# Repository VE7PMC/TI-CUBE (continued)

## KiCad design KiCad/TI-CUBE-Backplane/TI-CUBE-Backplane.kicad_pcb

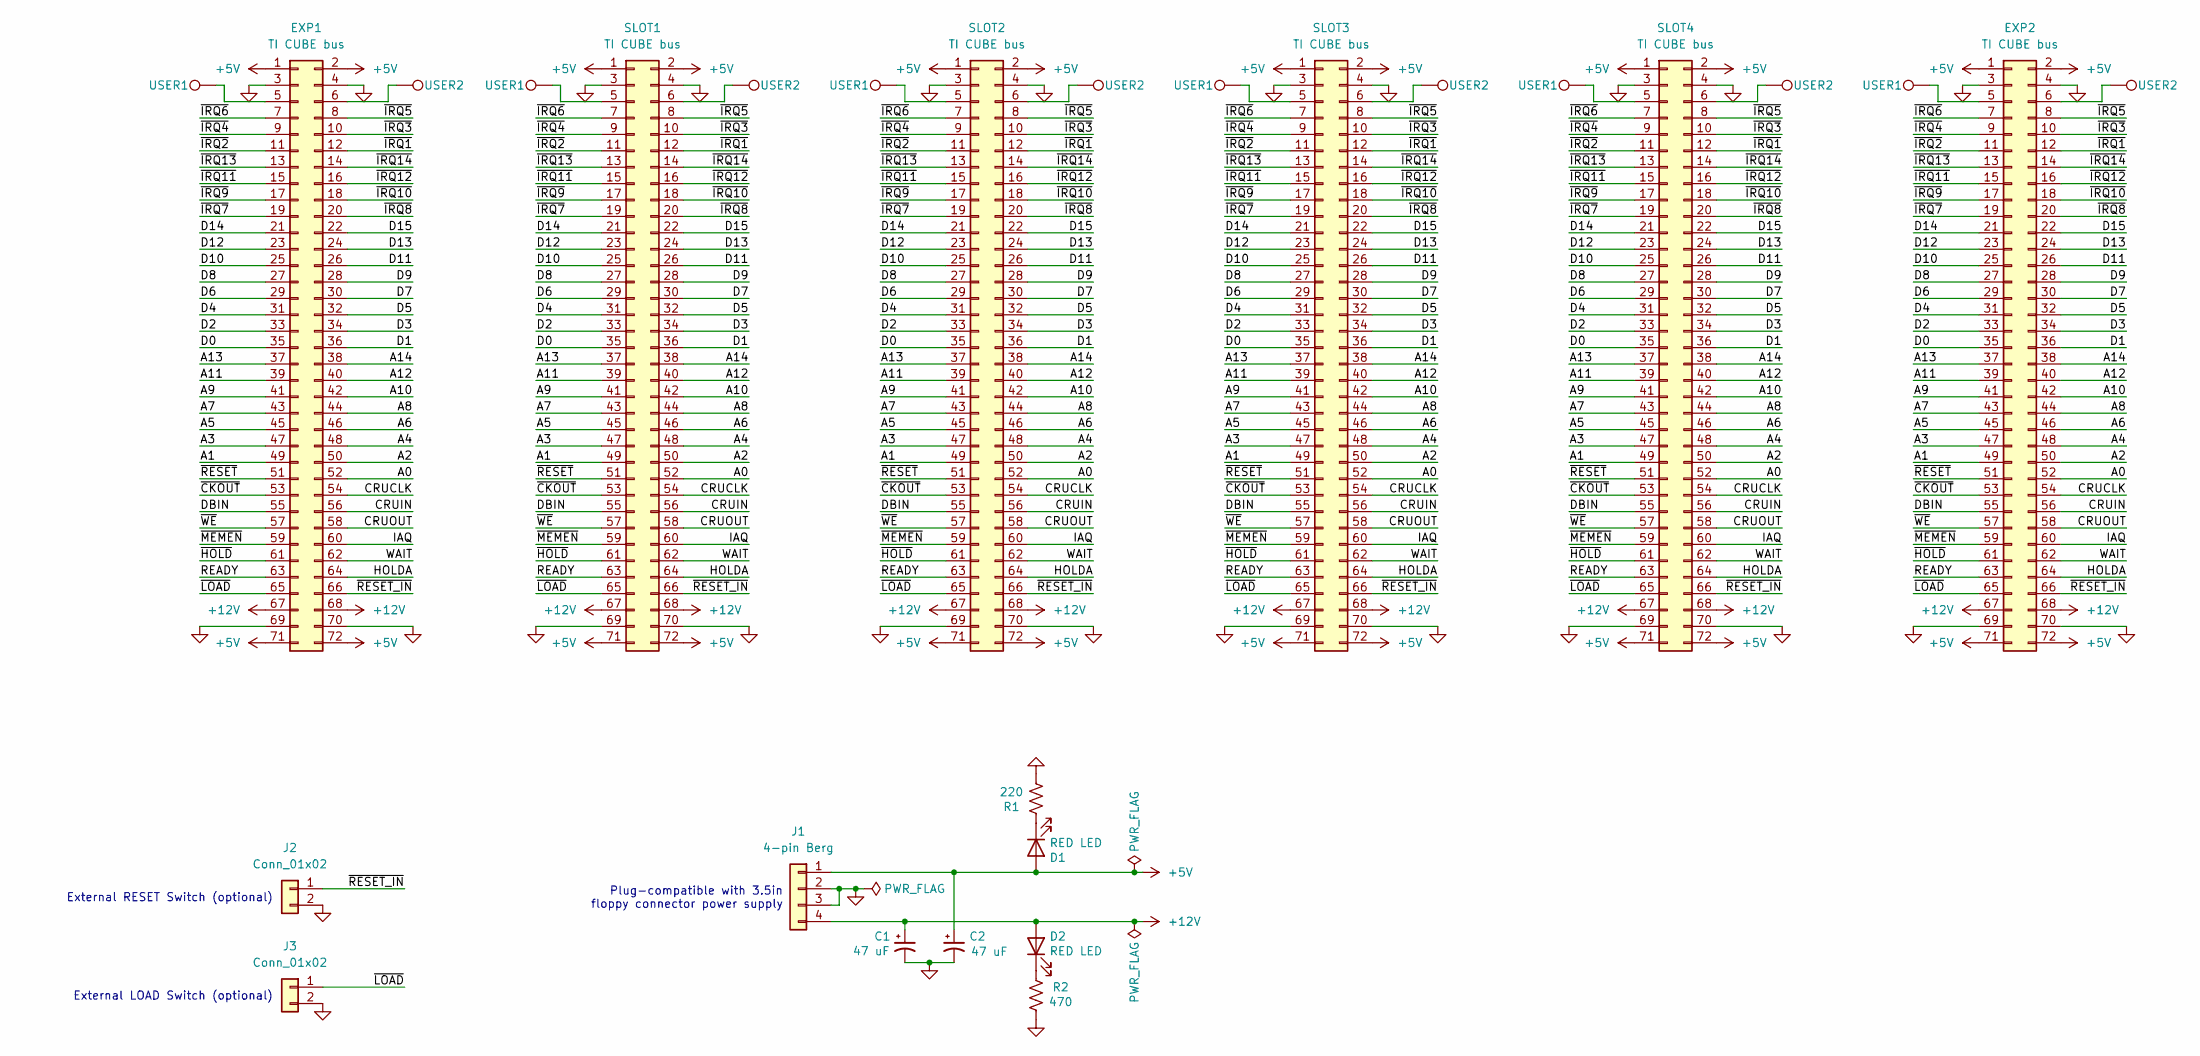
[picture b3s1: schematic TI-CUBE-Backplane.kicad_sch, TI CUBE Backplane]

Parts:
C1, C2: 47 uF; CP_Radial_D6.3mm_P2.50mm
D1, D2: RED LED; LED_D3.0mm
EXP1: TI CUBE bus; PinHeader_2x36_P2.54mm_Horizontal
EXP2: TI CUBE bus; PinSocket_2x36_P2.54mm_Horizontal
J1: 4-pin Berg; TE_171825-4
J2, J3: Conn_01x02; PinHeader_1x02_P2.54mm_Vertical
R1: 220; R_Axial_DIN0207_L6.3mm_D2.5mm_P10.16mm_Horizontal
R2: 470; R_Axial_DIN0207_L6.3mm_D2.5mm_P10.16mm_Horizontal
SLOT1, SLOT2, SLOT3, SLOT4: TI CUBE bus; PinSocket_2x36_P2.54mm_Vertical
USER1, USER4, USER5, USER7, USER9, USER11: USER1; TestPoint_THTPad_D1.5mm_Drill0.7mm
USER2, USER3, USER6, USER8, USER10, USER12: USER2; TestPoint_THTPad_D1.5mm_Drill0.7mm

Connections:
+5V: C2.1, D1.2 (A), EXP1.1, EXP1.2, EXP1.71, EXP1.72, EXP2.1, EXP2.2, EXP2.71, EXP2.72, J1.1, SLOT1.1, SLOT1.2, SLOT1.71, SLOT1.72, SLOT2.1, SLOT2.2, SLOT2.71, SLOT2.72, SLOT3.1, SLOT3.2, SLOT3.71, SLOT3.72, SLOT4.1, SLOT4.2, SLOT4.71, SLOT4.72
+12V: C1.1, D2.2 (A), EXP1.67, EXP1.68, EXP2.67, EXP2.68, J1.4, SLOT1.67, SLOT1.68, SLOT2.67, SLOT2.68, SLOT3.67, SLOT3.68, SLOT4.67, SLOT4.68
/A0: EXP1.52, EXP2.52, SLOT1.52, SLOT2.52, SLOT3.52, SLOT4.52
/A1: EXP1.49, EXP2.49, SLOT1.49, SLOT2.49, SLOT3.49, SLOT4.49
/A2: EXP1.50, EXP2.50, SLOT1.50, SLOT2.50, SLOT3.50, SLOT4.50
/A3: EXP1.47, EXP2.47, SLOT1.47, SLOT2.47, SLOT3.47, SLOT4.47
/A4: EXP1.48, EXP2.48, SLOT1.48, SLOT2.48, SLOT3.48, SLOT4.48
/A5: EXP1.45, EXP2.45, SLOT1.45, SLOT2.45, SLOT3.45, SLOT4.45
/A6: EXP1.46, EXP2.46, SLOT1.46, SLOT2.46, SLOT3.46, SLOT4.46
/A7: EXP1.43, EXP2.43, SLOT1.43, SLOT2.43, SLOT3.43, SLOT4.43
/A8: EXP1.44, EXP2.44, SLOT1.44, SLOT2.44, SLOT3.44, SLOT4.44
/A9: EXP1.41, EXP2.41, SLOT1.41, SLOT2.41, SLOT3.41, SLOT4.41
/A10: EXP1.42, EXP2.42, SLOT1.42, SLOT2.42, SLOT3.42, SLOT4.42
/A11: EXP1.39, EXP2.39, SLOT1.39, SLOT2.39, SLOT3.39, SLOT4.39
/A12: EXP1.40, EXP2.40, SLOT1.40, SLOT2.40, SLOT3.40, SLOT4.40
/A13: EXP1.37, EXP2.37, SLOT1.37, SLOT2.37, SLOT3.37, SLOT4.37
/A14: EXP1.38, EXP2.38, SLOT1.38, SLOT2.38, SLOT3.38, SLOT4.38
/CRUCLK: EXP1.54, EXP2.54, SLOT1.54, SLOT2.54, SLOT3.54, SLOT4.54
/CRUIN: EXP1.56, EXP2.56, SLOT1.56, SLOT2.56, SLOT3.56, SLOT4.56
/CRUOUT: EXP1.58, EXP2.58, SLOT1.58, SLOT2.58, SLOT3.58, SLOT4.58
/D0: EXP1.35, EXP2.35, SLOT1.35, SLOT2.35, SLOT3.35, SLOT4.35
/D1: EXP1.36, EXP2.36, SLOT1.36, SLOT2.36, SLOT3.36, SLOT4.36
/D2: EXP1.33, EXP2.33, SLOT1.33, SLOT2.33, SLOT3.33, SLOT4.33
/D3: EXP1.34, EXP2.34, SLOT1.34, SLOT2.34, SLOT3.34, SLOT4.34
/D4: EXP1.31, EXP2.31, SLOT1.31, SLOT2.31, SLOT3.31, SLOT4.31
/D5: EXP1.32, EXP2.32, SLOT1.32, SLOT2.32, SLOT3.32, SLOT4.32
/D6: EXP1.29, EXP2.29, SLOT1.29, SLOT2.29, SLOT3.29, SLOT4.29
/D7: EXP1.30, EXP2.30, SLOT1.30, SLOT2.30, SLOT3.30, SLOT4.30
/D8: EXP1.27, EXP2.27, SLOT1.27, SLOT2.27, SLOT3.27, SLOT4.27
/D9: EXP1.28, EXP2.28, SLOT1.28, SLOT2.28, SLOT3.28, SLOT4.28
/D10: EXP1.25, EXP2.25, SLOT1.25, SLOT2.25, SLOT3.25, SLOT4.25
/D11: EXP1.26, EXP2.26, SLOT1.26, SLOT2.26, SLOT3.26, SLOT4.26
/D12: EXP1.23, EXP2.23, SLOT1.23, SLOT2.23, SLOT3.23, SLOT4.23
/D13: EXP1.24, EXP2.24, SLOT1.24, SLOT2.24, SLOT3.24, SLOT4.24
/D14: EXP1.21, EXP2.21, SLOT1.21, SLOT2.21, SLOT3.21, SLOT4.21
/D15: EXP1.22, EXP2.22, SLOT1.22, SLOT2.22, SLOT3.22, SLOT4.22
/DBIN: EXP1.55, EXP2.55, SLOT1.55, SLOT2.55, SLOT3.55, SLOT4.55
/HOLDA: EXP1.64, EXP2.64, SLOT1.64, SLOT2.64, SLOT3.64, SLOT4.64
/IAQ: EXP1.60, EXP2.60, SLOT1.60, SLOT2.60, SLOT3.60, SLOT4.60
/READY: EXP1.63, EXP2.63, SLOT1.63, SLOT2.63, SLOT3.63, SLOT4.63
/WAIT: EXP1.62, EXP2.62, SLOT1.62, SLOT2.62, SLOT3.62, SLOT4.62
/~CKOUT: EXP1.53, EXP2.53, SLOT1.53, SLOT2.53, SLOT3.53, SLOT4.53
/~HOLD: EXP1.61, EXP2.61, SLOT1.61, SLOT2.61, SLOT3.61, SLOT4.61
/~IRQ1: EXP1.12, EXP2.12, SLOT1.12, SLOT2.12, SLOT3.12, SLOT4.12
/~IRQ2: EXP1.11, EXP2.11, SLOT1.11, SLOT2.11, SLOT3.11, SLOT4.11
/~IRQ3: EXP1.10, EXP2.10, SLOT1.10, SLOT2.10, SLOT3.10, SLOT4.10
/~IRQ4: EXP1.9, EXP2.9, SLOT1.9, SLOT2.9, SLOT3.9, SLOT4.9
/~IRQ5: EXP1.8, EXP2.8, SLOT1.8, SLOT2.8, SLOT3.8, SLOT4.8
/~IRQ6: EXP1.7, EXP2.7, SLOT1.7, SLOT2.7, SLOT3.7, SLOT4.7
/~IRQ7: EXP1.19, EXP2.19, SLOT1.19, SLOT2.19, SLOT3.19, SLOT4.19
/~IRQ8: EXP1.20, EXP2.20, SLOT1.20, SLOT2.20, SLOT3.20, SLOT4.20
/~IRQ9: EXP1.17, EXP2.17, SLOT1.17, SLOT2.17, SLOT3.17, SLOT4.17
/~IRQ10: EXP1.18, EXP2.18, SLOT1.18, SLOT2.18, SLOT3.18, SLOT4.18
/~IRQ11: EXP1.15, EXP2.15, SLOT1.15, SLOT2.15, SLOT3.15, SLOT4.15
/~IRQ12: EXP1.16, EXP2.16, SLOT1.16, SLOT2.16, SLOT3.16, SLOT4.16
/~IRQ13: EXP1.13, EXP2.13, SLOT1.13, SLOT2.13, SLOT3.13, SLOT4.13
/~IRQ14: EXP1.14, EXP2.14, SLOT1.14, SLOT2.14, SLOT3.14, SLOT4.14
/~LOAD: EXP1.65, EXP2.65, J3.1, SLOT1.65, SLOT2.65, SLOT3.65, SLOT4.65
/~MEMEN: EXP1.59, EXP2.59, SLOT1.59, SLOT2.59, SLOT3.59, SLOT4.59
/~RESET_IN: EXP1.66, EXP2.66, J2.1, SLOT1.66, SLOT2.66, SLOT3.66, SLOT4.66
/~RESET: EXP1.51, EXP2.51, SLOT1.51, SLOT2.51, SLOT3.51, SLOT4.51
/~WE: EXP1.57, EXP2.57, SLOT1.57, SLOT2.57, SLOT3.57, SLOT4.57
GND: C1.2, C2.2, EXP1.3, EXP1.4, EXP1.69, EXP1.70, EXP2.3, EXP2.4, EXP2.69, EXP2.70, J1.2, J1.3, J2.2, J3.2, R1.1, R2.1, SLOT1.3, SLOT1.4, SLOT1.69, SLOT1.70, SLOT2.3, SLOT2.4, SLOT2.69, SLOT2.70, SLOT3.3, SLOT3.4, SLOT3.69, SLOT3.70, SLOT4.3, SLOT4.4, SLOT4.69, SLOT4.70
unnamed: D1.1 (K), R1.2
unnamed: D2.1 (K), R2.2
unnamed: EXP1.5, USER1.1
unnamed: EXP1.6, USER2.1
unnamed: EXP2.5, USER11.1
unnamed: EXP2.6, USER12.1
unnamed: SLOT1.5, USER4.1
unnamed: SLOT1.6, USER3.1
unnamed: SLOT2.5, USER5.1
unnamed: SLOT2.6, USER6.1
unnamed: SLOT3.5, USER7.1
unnamed: SLOT3.6, USER8.1
unnamed: SLOT4.5, USER9.1
unnamed: SLOT4.6, USER10.1

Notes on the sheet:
Plug-compatible with 3.5in floppy connector power supply
External LOAD Switch (optional)
External RESET Switch (optional)

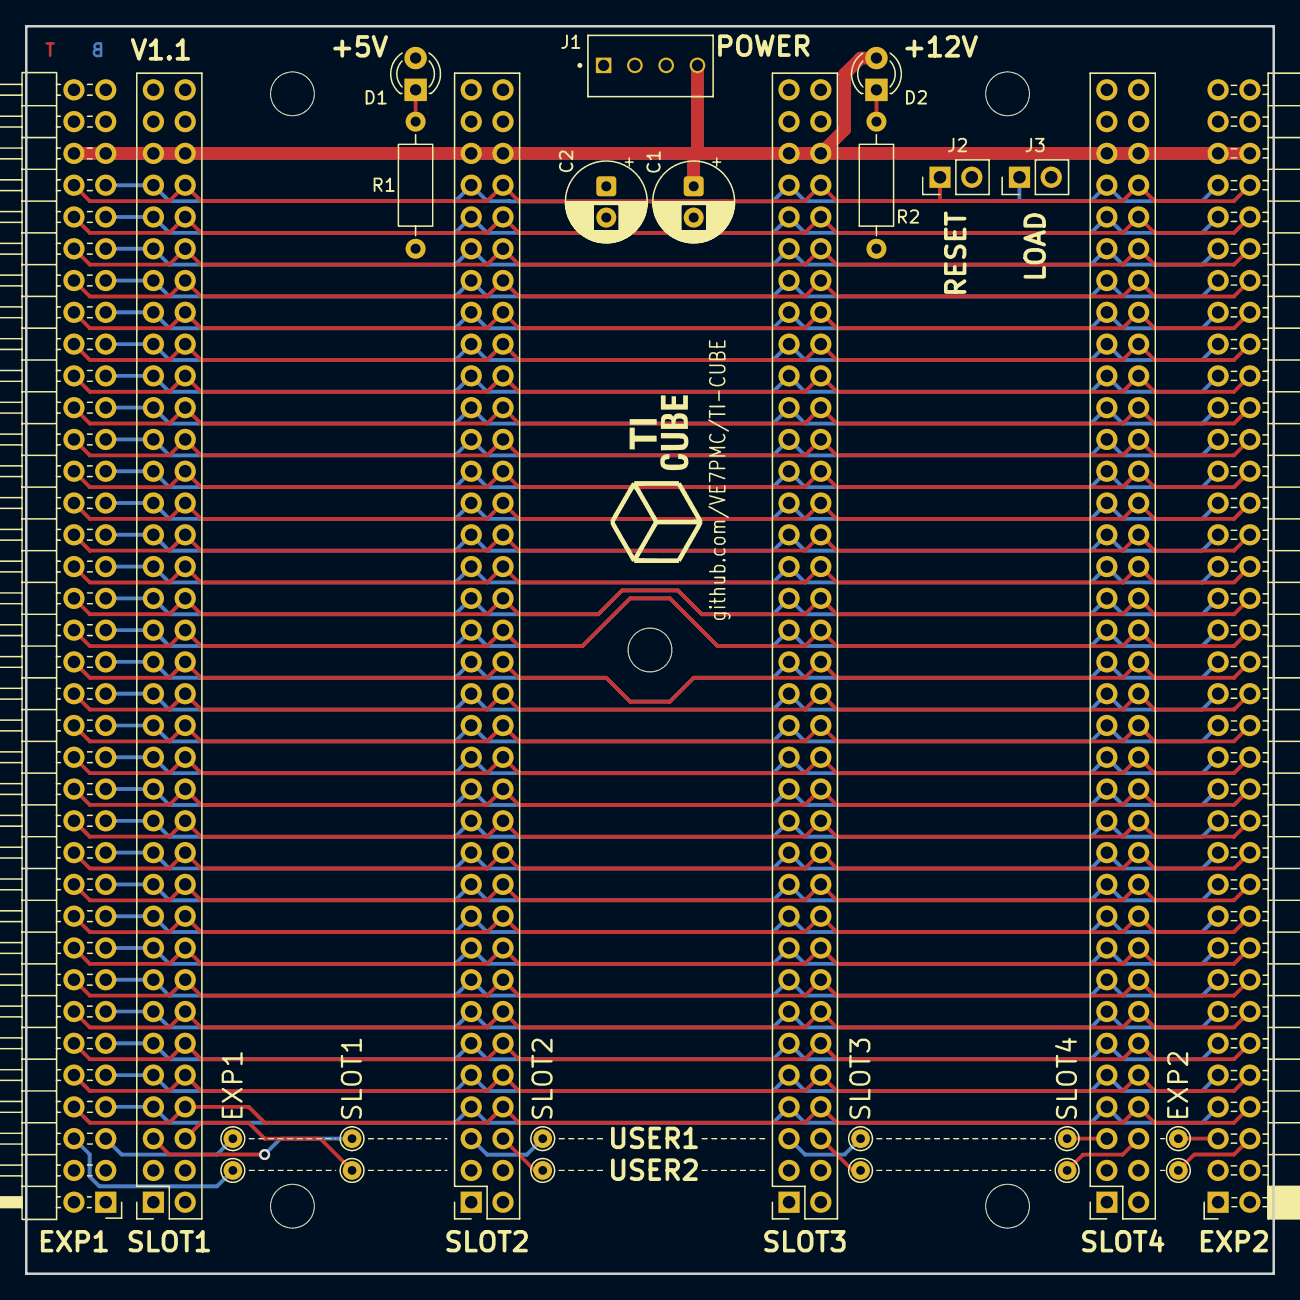
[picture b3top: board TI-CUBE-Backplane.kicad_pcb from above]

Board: 4 copper layers, 99.7 x 99.7 mm, 27 parts (0 on the bottom side), 77 nets.

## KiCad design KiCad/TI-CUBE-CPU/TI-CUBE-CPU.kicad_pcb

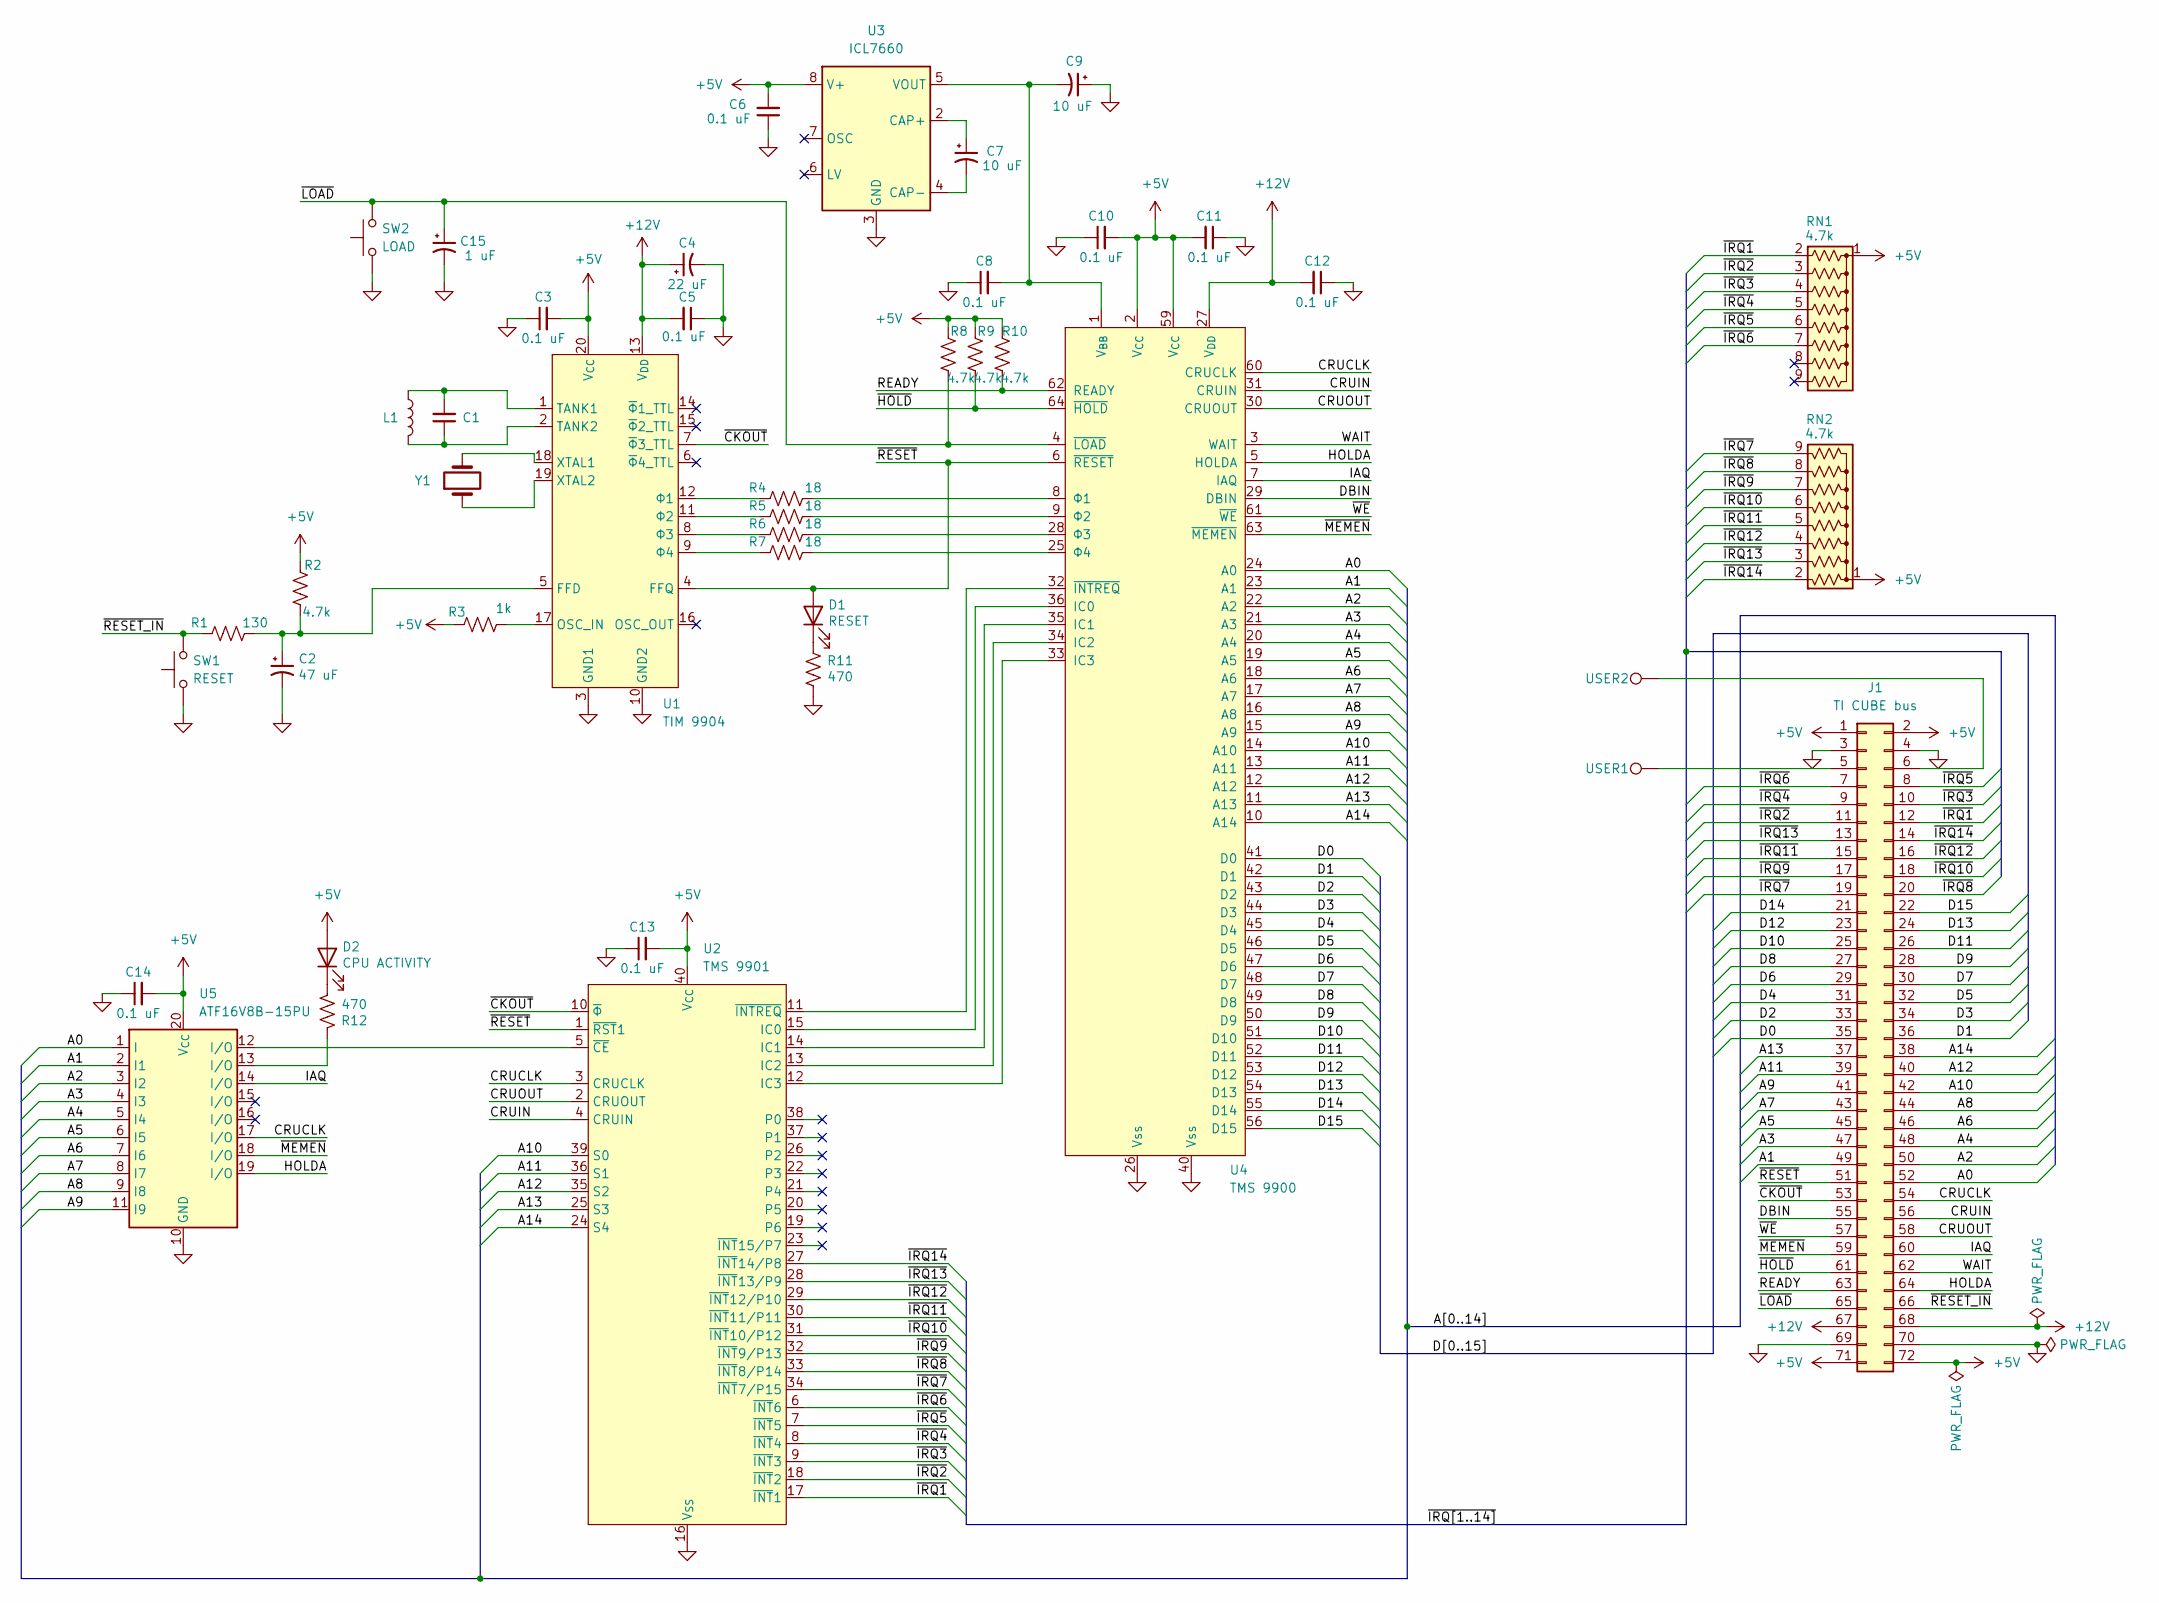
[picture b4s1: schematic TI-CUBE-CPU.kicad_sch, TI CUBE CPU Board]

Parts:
C1: 18 pF; C_Ceramic_Cap_P2.50mm
C2: 47 uF; CP_Radial_D5.0mm_P2.50mm
C3, C5, C6, C8, C10, C11, C12, C13, C14: 0.1 uF; C_Ceramic_Cap_P2.50mm
C4: 22 uF; CP_Radial_D5.0mm_P2.50mm
C7, C9: 10 uF; CP_Radial_D5.0mm_P2.50mm
C15: 1 uF; CP_Radial_D5.0mm_P2.50mm
D1: RESET; LED_D3.0mm_Horizontal_O1.27mm_Z2.0mm
D2: CPU ACTIVITY; LED_D3.0mm_Horizontal_O1.27mm_Z2.0mm
J1: TI CUBE bus; PinHeader_2x36_P2.54mm_Horizontal
L1: 0.47 uH; L_Axial_L6.6mm_D2.7mm_P2.54mm_Vertical_Vishay_IM-2
R1: 130; R_Axial_DIN0207_L6.3mm_D2.5mm_P7.62mm_Horizontal
R2, R8, R9, R10: 4.7k; R_Axial_DIN0207_L6.3mm_D2.5mm_P7.62mm_Horizontal
R3: 1k; R_Axial_DIN0207_L6.3mm_D2.5mm_P7.62mm_Horizontal
R4, R5, R6, R7: 18; R_Axial_DIN0207_L6.3mm_D2.5mm_P7.62mm_Horizontal
R11, R12: 470; R_Axial_DIN0207_L6.3mm_D2.5mm_P7.62mm_Horizontal
RN1, RN2: 4.7k; R_Array_SIP9
SW1: RESET; SW_SPST_Omron_B3F-315x_Angled
SW2: LOAD; SW_SPST_Omron_B3F-315x_Angled
U1: TIM 9904; DIP-20_W7.62mm
U2: TMS 9901; DIP-40_W15.24mm
U3: ICL7660; DIP-8_W7.62mm
U4: TMS 9900; DIP-64_W22.86mm
U5: ATF16V8B-15PU; DIP-20_W7.62mm
USER1: USER1; TestPoint_THTPad_D1.5mm_Drill0.7mm
USER2: USER2; TestPoint_THTPad_D1.5mm_Drill0.7mm
Y1: 48 MHz; Crystal_HC49-4H_Vertical

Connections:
+5V: C3.2, C6.2, C10.2, C11.2, C13.2, C14.2, D2.2 (A), J1.1, J1.2, J1.71, J1.72, R2.2, R3.2, R8.2, R9.2, R10.2, RN1.1 (common), RN2.1 (common), U1.20 (V_{CC}), U2.40 (V_{CC}), U3.8 (V+), U4.2 (V_{CC}), U4.59 (V_{CC}), U5.20 (V_{CC})
+12V: C4.1, C5.2, C12.2, J1.67, J1.68, U1.13 (V_{DD}), U4.27 (V_{DD})
/A0: J1.52, U4.24 (A0), U5.1 (I)
/A1: J1.49, U4.23 (A1), U5.2 (I1)
/A2: J1.50, U4.22 (A2), U5.3 (I2)
/A3: J1.47, U4.21 (A3), U5.4 (I3)
/A4: J1.48, U4.20 (A4), U5.5 (I4)
/A5: J1.45, U4.19 (A5), U5.6 (I5)
/A6: J1.46, U4.18 (A6), U5.7 (I6)
/A7: J1.43, U4.17 (A7), U5.8 (I7)
/A8: J1.44, U4.16 (A8), U5.9 (I8)
/A9: J1.41, U4.15 (A9), U5.11 (I9)
/A10: J1.42, U2.39 (S0), U4.14 (A10)
/A11: J1.39, U2.36 (S1), U4.13 (A11)
/A12: J1.40, U2.35 (S2), U4.12 (A12)
/A13: J1.37, U2.25 (S3), U4.11 (A13)
/A14: J1.38, U2.24 (S4), U4.10 (A14)
/CRUCLK: J1.54, U2.3 (CRUCLK), U4.60 (CRUCLK), U5.17 (I/O)
/CRUIN: J1.56, U2.4 (CRUIN), U4.31 (CRUIN)
/CRUOUT: J1.58, U2.2 (CRUOUT), U4.30 (CRUOUT)
/D0: J1.35, U4.41 (D0)
/D1: J1.36, U4.42 (D1)
/D2: J1.33, U4.43 (D2)
/D3: J1.34, U4.44 (D3)
/D4: J1.31, U4.45 (D4)
/D5: J1.32, U4.46 (D5)
/D6: J1.29, U4.47 (D6)
/D7: J1.30, U4.48 (D7)
/D8: J1.27, U4.49 (D8)
/D9: J1.28, U4.50 (D9)
/D10: J1.25, U4.51 (D10)
/D11: J1.26, U4.52 (D11)
/D12: J1.23, U4.53 (D12)
/D13: J1.24, U4.54 (D13)
/D14: J1.21, U4.55 (D14)
/D15: J1.22, U4.56 (D15)
/DBIN: J1.55, U4.29 (DBIN)
/HOLDA: J1.64, U4.5 (HOLDA), U5.19 (I/O)
/IAQ: J1.60, U4.7 (IAQ), U5.14 (I/O)
/READY: J1.63, R10.1, U4.62 (READY)
/WAIT: J1.62, U4.3 (WAIT)
/~CKOUT: J1.53, U1.7 (~Φ3_TTL), U2.10 (~Φ)
/~HOLD: J1.61, R9.1, U4.64 (~HOLD)
/~IRQ1: J1.12, RN1.2 (R1), U2.17 (~INT1)
/~IRQ2: J1.11, RN1.3 (R2), U2.18 (~INT2)
/~IRQ3: J1.10, RN1.4 (R3), U2.9 (~INT3)
/~IRQ4: J1.9, RN1.5 (R4), U2.8 (~INT4)
/~IRQ5: J1.8, RN1.6 (R5), U2.7 (~INT5)
/~IRQ6: J1.7, RN1.7 (R6), U2.6 (~INT6)
/~IRQ7: J1.19, RN2.9 (R8), U2.34 (~INT7/P15)
/~IRQ8: J1.20, RN2.8 (R7), U2.33 (~INT8/P14)
/~IRQ9: J1.17, RN2.7 (R6), U2.32 (~INT9/P13)
/~IRQ10: J1.18, RN2.6 (R5), U2.31 (~INT10/P12)
/~IRQ11: J1.15, RN2.5 (R4), U2.30 (~INT11/P11)
/~IRQ12: J1.16, RN2.4 (R3), U2.29 (~INT12/P10)
/~IRQ13: J1.13, RN2.3 (R2), U2.28 (~INT13/P9)
/~IRQ14: J1.14, RN2.2 (R1), U2.27 (~INT14/P8)
/~LOAD: C15.1, J1.65, R8.1, SW2.2, U4.4 (~LOAD)
/~MEMEN: J1.59, U4.63 (~MEMEN), U5.18 (I/O)
/~RESET_IN: J1.66, R1.1, SW1.2
/~RESET: D1.2 (A), J1.51, U1.4 (FFQ), U2.1 (~RST1), U4.6 (~RESET)
/~WE: J1.57, U4.61 (~WE)
GND: C2.2, C3.1, C4.2, C5.1, C6.1, C8.1, C9.1, C10.1, C11.1, C12.1, C13.1, C14.1, C15.2, J1.3, J1.4, J1.69, J1.70, R11.1, SW1.1, SW2.1, U1.3 (GND1), U1.10 (GND2), U2.16 (V_{SS}), U3.3 (GND), U4.26 (Vss), U4.40 (Vss), U5.10 (GND)
unnamed: D1.1 (K), R11.2
unnamed: D2.1 (K), R12.1
unnamed: J1.5, USER1.1
unnamed: J1.6, USER2.1
unnamed: R12.2, U5.13 (I/O)
unnamed: C2.1, R1.2, R2.1, U1.5 (FFD)
unnamed: R3.1, U1.17 (OSC_IN)
unnamed: C1.2, L1.2, U1.1 (TANK1)
unnamed: C1.1, L1.1, U1.2 (TANK2)
unnamed: U1.18 (XTAL1), Y1.2
unnamed: U1.19 (XTAL2), Y1.1
unnamed: R4.1, U1.12 (Φ1)
unnamed: R5.1, U1.11 (Φ2)
unnamed: R6.1, U1.8 (Φ3)
unnamed: R7.1, U1.9 (Φ4)
unnamed: U2.15 (IC0), U4.36 (IC0)
unnamed: U2.14 (IC1), U4.35 (IC1)
unnamed: U2.13 (IC2), U4.34 (IC2)
unnamed: U2.12 (IC3), U4.33 (IC3)
unnamed: U2.5 (~CE), U5.12 (I/O)
unnamed: U2.11 (~INTREQ), U4.32 (~INTREQ)
unnamed: C7.1, U3.2 (CAP+)
unnamed: C7.2, U3.4 (CAP-)
unnamed: C8.2, C9.2, U3.5 (VOUT), U4.1 (V_{BB})
unnamed: R4.2, U4.8 (Φ1)
unnamed: R5.2, U4.9 (Φ2)
unnamed: R6.2, U4.28 (Φ3)
unnamed: R7.2, U4.25 (Φ4)

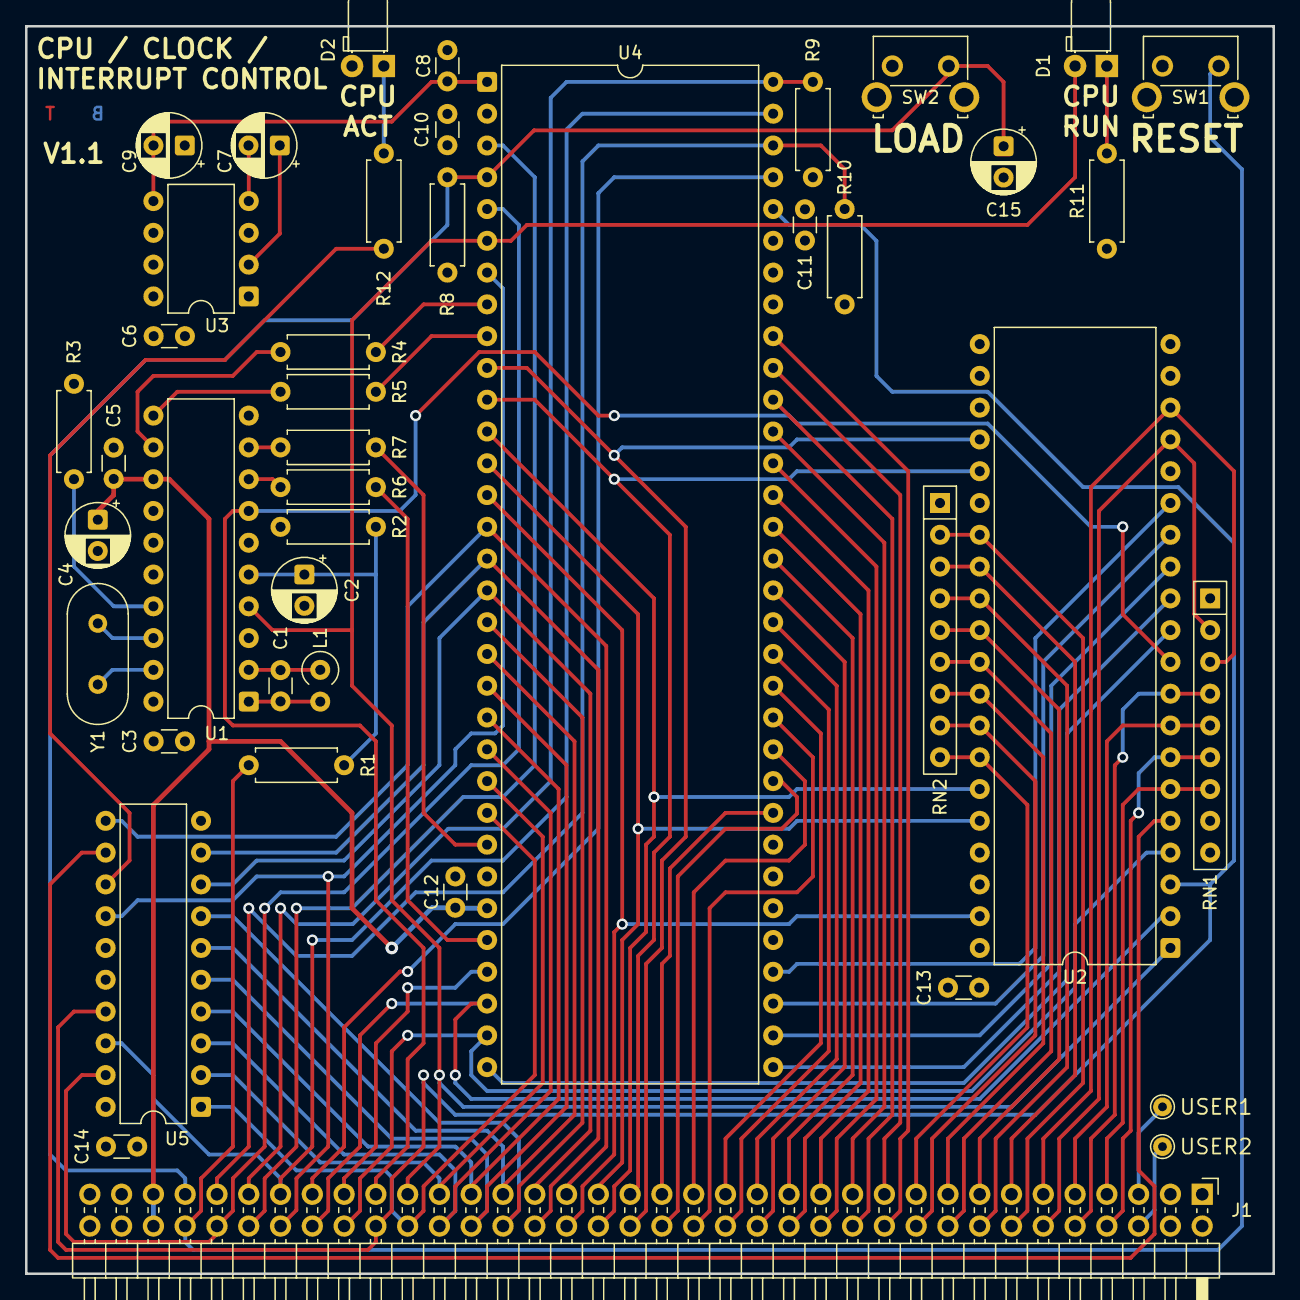
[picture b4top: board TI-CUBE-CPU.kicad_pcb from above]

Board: 4 copper layers, 99.7 x 99.7 mm, 43 parts (0 on the bottom side), 91 nets.

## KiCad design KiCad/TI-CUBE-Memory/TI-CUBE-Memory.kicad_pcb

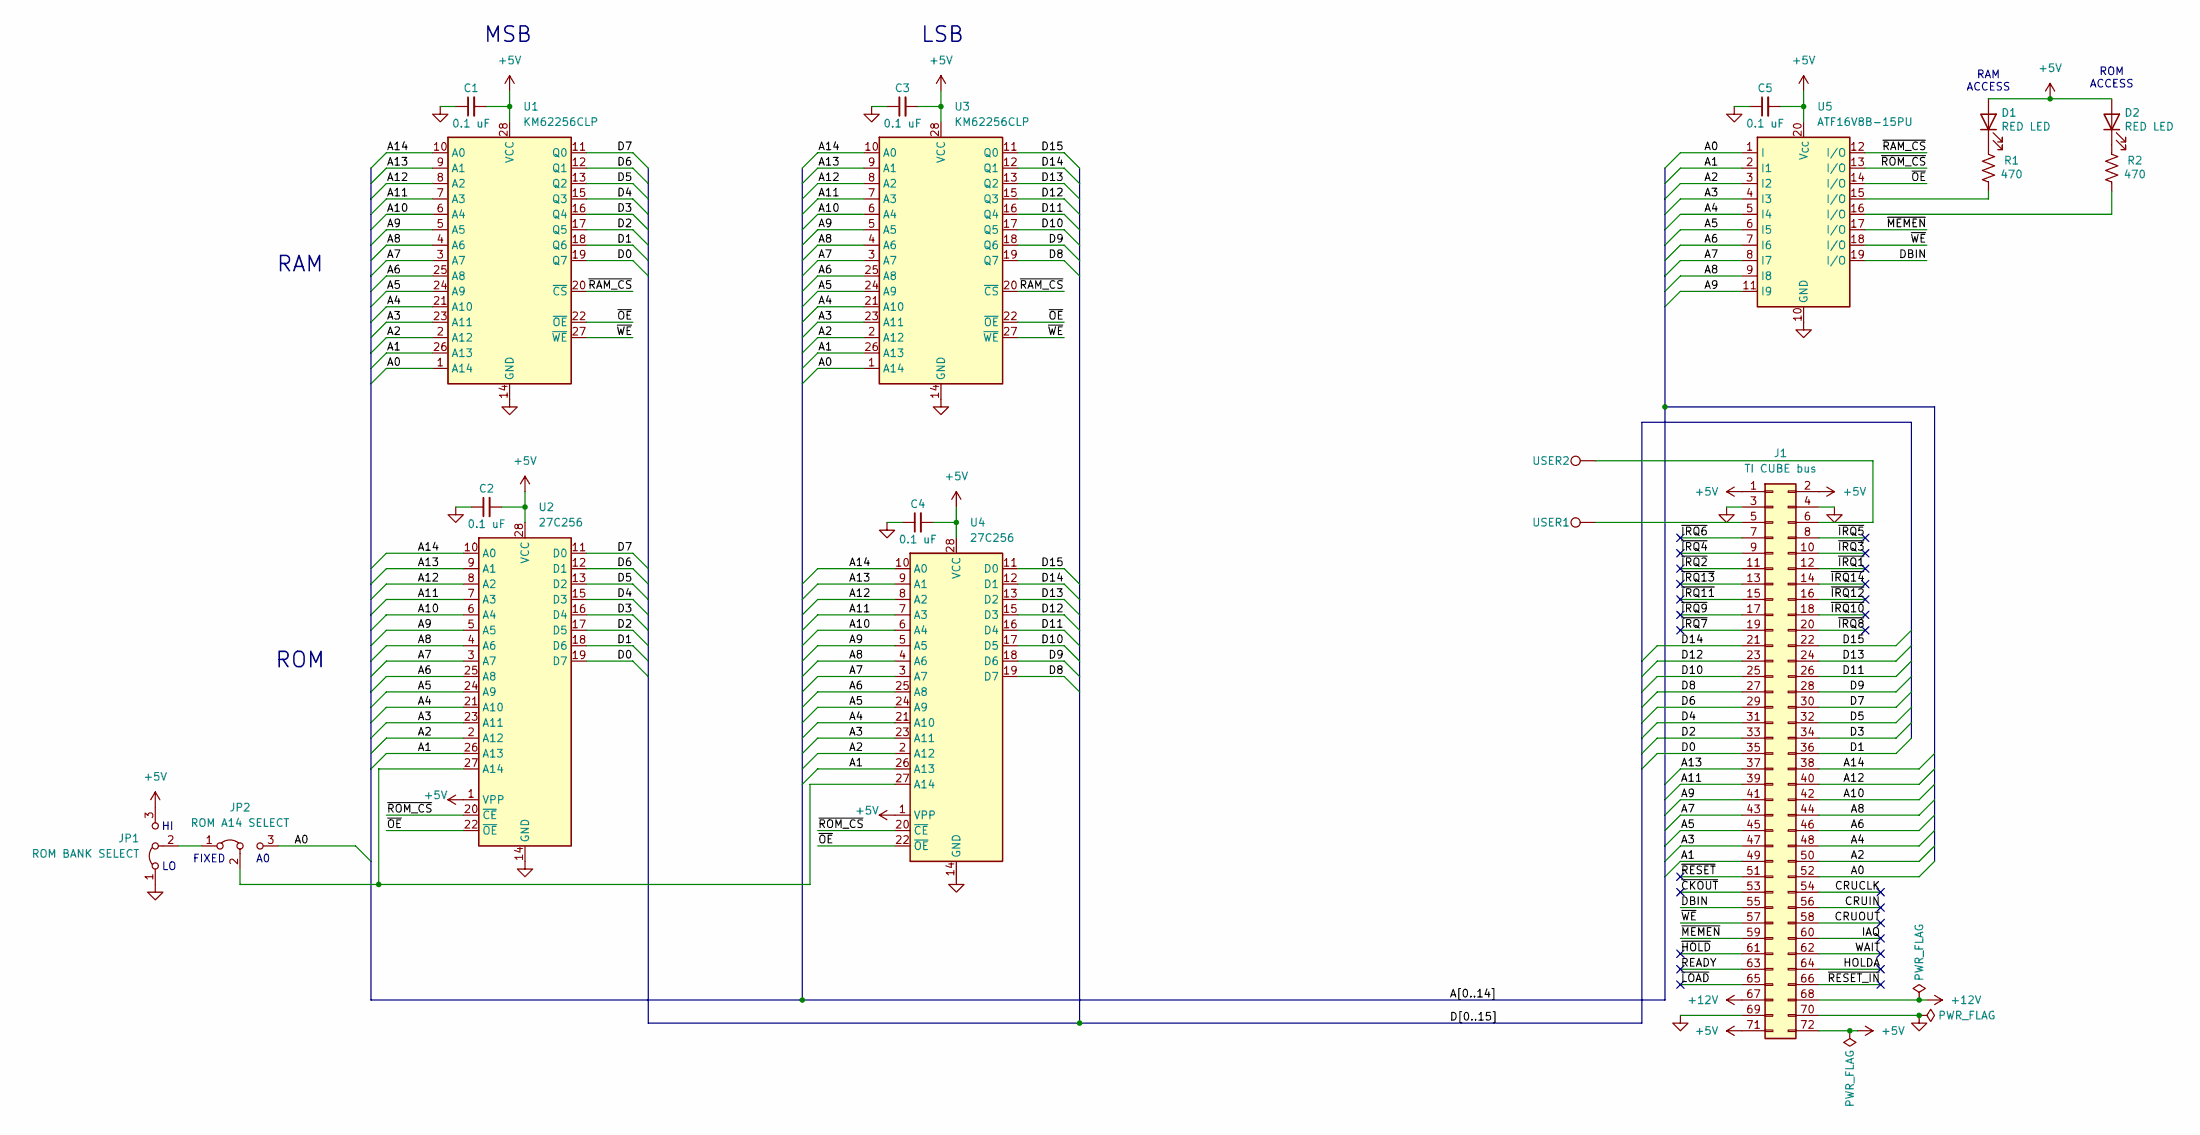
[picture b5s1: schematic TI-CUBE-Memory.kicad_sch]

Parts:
C1, C2, C3, C4, C5: 0.1 uF; C_Ceramic_Cap_P2.50mm
D1, D2: RED LED; LED_D3.0mm_Horizontal_O1.27mm_Z2.0mm
J1: TI CUBE bus; PinHeader_2x36_P2.54mm_Horizontal
JP1: ROM BANK SELECT; PinHeader_1x03_P2.54mm_Vertical
JP2: ROM A14 SELECT; PinHeader_1x03_P2.54mm_Vertical
R1, R2: 470; R_Axial_DIN0207_L6.3mm_D2.5mm_P10.16mm_Horizontal
U1, U3: KM62256CLP; DIP-28_W15.24mm
U2, U4: 27C256; DIP-28_W15.24mm
U5: ATF16V8B-15PU; DIP-20_W7.62mm
USER1: USER1; TestPoint_THTPad_D1.5mm_Drill0.7mm
USER2: USER2; TestPoint_THTPad_D1.5mm_Drill0.7mm

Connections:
+5V: C1.2, C2.2, C3.2, C4.2, C5.2, D1.2 (A), D2.2 (A), J1.1, J1.2, J1.71, J1.72, JP1.3 (B), U1.28 (VCC), U2.1 (VPP), U2.28 (VCC), U3.28 (VCC), U4.1 (VPP), U4.28 (VCC), U5.20 (V_{CC})
+12V: J1.67, J1.68
/A0: J1.52, JP2.3 (B), U1.1 (A14), U3.1 (A14), U5.1 (I)
/A1: J1.49, U1.26 (A13), U2.26 (A13), U3.26 (A13), U4.26 (A13), U5.2 (I1)
/A2: J1.50, U1.2 (A12), U2.2 (A12), U3.2 (A12), U4.2 (A12), U5.3 (I2)
/A3: J1.47, U1.23 (A11), U2.23 (A11), U3.23 (A11), U4.23 (A11), U5.4 (I3)
/A4: J1.48, U1.21 (A10), U2.21 (A10), U3.21 (A10), U4.21 (A10), U5.5 (I4)
/A5: J1.45, U1.24 (A9), U2.24 (A9), U3.24 (A9), U4.24 (A9), U5.6 (I5)
/A6: J1.46, U1.25 (A8), U2.25 (A8), U3.25 (A8), U4.25 (A8), U5.7 (I6)
/A7: J1.43, U1.3 (A7), U2.3 (A7), U3.3 (A7), U4.3 (A7), U5.8 (I7)
/A8: J1.44, U1.4 (A6), U2.4 (A6), U3.4 (A6), U4.4 (A6), U5.9 (I8)
/A9: J1.41, U1.5 (A5), U2.5 (A5), U3.5 (A5), U4.5 (A5), U5.11 (I9)
/A10: J1.42, U1.6 (A4), U2.6 (A4), U3.6 (A4), U4.6 (A4)
/A11: J1.39, U1.7 (A3), U2.7 (A3), U3.7 (A3), U4.7 (A3)
/A12: J1.40, U1.8 (A2), U2.8 (A2), U3.8 (A2), U4.8 (A2)
/A13: J1.37, U1.9 (A1), U2.9 (A1), U3.9 (A1), U4.9 (A1)
/A14: J1.38, U1.10 (A0), U2.10 (A0), U3.10 (A0), U4.10 (A0)
/CRUCLK: J1.54
/CRUIN: J1.56
/CRUOUT: J1.58
/D0: J1.35, U1.19 (Q7), U2.19 (D7)
/D1: J1.36, U1.18 (Q6), U2.18 (D6)
/D2: J1.33, U1.17 (Q5), U2.17 (D5)
/D3: J1.34, U1.16 (Q4), U2.16 (D4)
/D4: J1.31, U1.15 (Q3), U2.15 (D3)
/D5: J1.32, U1.13 (Q2), U2.13 (D2)
/D6: J1.29, U1.12 (Q1), U2.12 (D1)
/D7: J1.30, U1.11 (Q0), U2.11 (D0)
/D8: J1.27, U3.19 (Q7), U4.19 (D7)
/D9: J1.28, U3.18 (Q6), U4.18 (D6)
/D10: J1.25, U3.17 (Q5), U4.17 (D5)
/D11: J1.26, U3.16 (Q4), U4.16 (D4)
/D12: J1.23, U3.15 (Q3), U4.15 (D3)
/D13: J1.24, U3.13 (Q2), U4.13 (D2)
/D14: J1.21, U3.12 (Q1), U4.12 (D1)
/D15: J1.22, U3.11 (Q0), U4.11 (D0)
/DBIN: J1.55, U5.19 (I/O)
/HOLDA: J1.64
/IAQ: J1.60
/READY: J1.63
/WAIT: J1.62
/~CKOUT: J1.53
/~HOLD: J1.61
/~IRQ1: J1.12
/~IRQ2: J1.11
/~IRQ3: J1.10
/~IRQ4: J1.9
/~IRQ5: J1.8
/~IRQ6: J1.7
/~IRQ7: J1.19
/~IRQ8: J1.20
/~IRQ9: J1.17
/~IRQ10: J1.18
/~IRQ11: J1.15
/~IRQ12: J1.16
/~IRQ13: J1.13
/~IRQ14: J1.14
/~LOAD: J1.65
/~MEMEN: J1.59, U5.17 (I/O)
/~OE: U1.22 (~OE), U2.22 (~OE), U3.22 (~OE), U4.22 (~OE), U5.14 (I/O)
/~RAM_CS: U1.20 (~CS), U3.20 (~CS), U5.12 (I/O)
/~RESET_IN: J1.66
/~RESET: J1.51
/~ROM_CS: U2.20 (~CE), U4.20 (~CE), U5.13 (I/O)
/~WE: J1.57, U1.27 (~WE), U3.27 (~WE), U5.18 (I/O)
GND: C1.1, C2.1, C3.1, C4.1, C5.1, J1.3, J1.4, J1.69, J1.70, JP1.1 (A), U1.14 (GND), U2.14 (GND), U3.14 (GND), U4.14 (GND), U5.10 (GND)
unnamed: D1.1 (K), R1.2
unnamed: D2.1 (K), R2.2
unnamed: J1.5, USER1.1
unnamed: J1.6, USER2.1
unnamed: JP1.2 (C), JP2.1 (A)
unnamed: JP2.2 (C), U2.27 (A14), U4.27 (A14)
unnamed: R1.1, U5.15 (I/O)
unnamed: R2.1, U5.16 (I/O)

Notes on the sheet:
ROM
RAM
FIXED
MSB
RAM ACCESS
LSB
ROM ACCESS

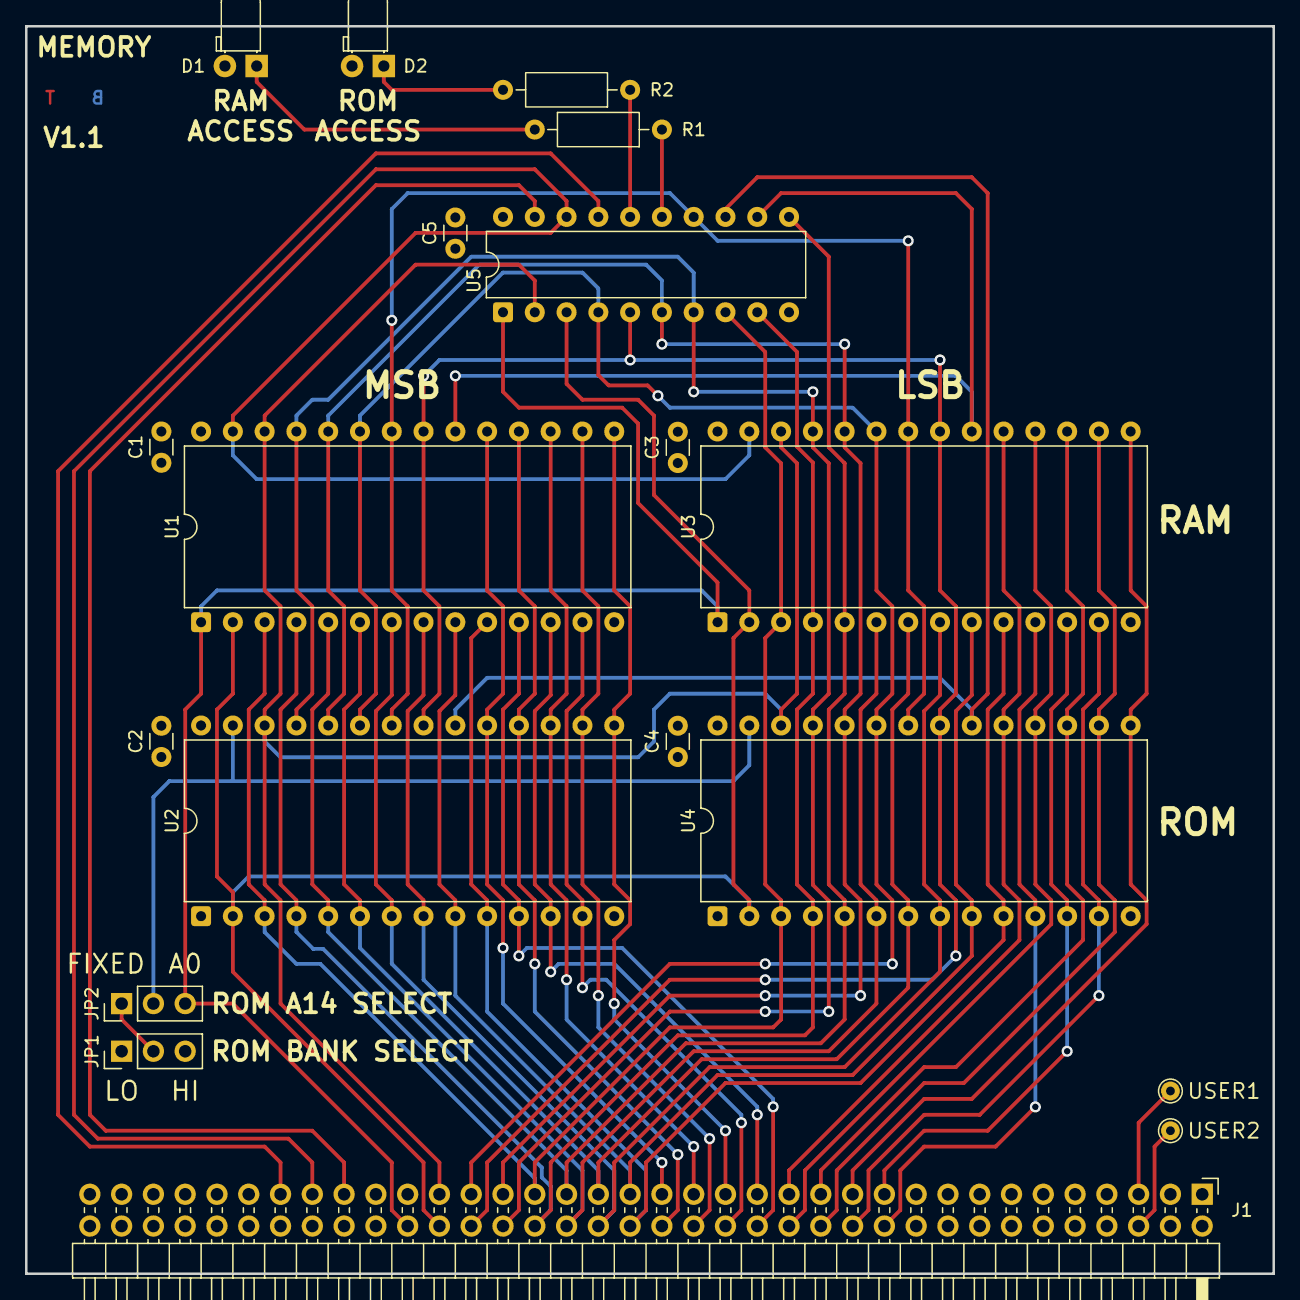
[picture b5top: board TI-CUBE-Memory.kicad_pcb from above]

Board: 4 copper layers, 99.7 x 99.7 mm, 19 parts (0 on the bottom side), 48 nets.
